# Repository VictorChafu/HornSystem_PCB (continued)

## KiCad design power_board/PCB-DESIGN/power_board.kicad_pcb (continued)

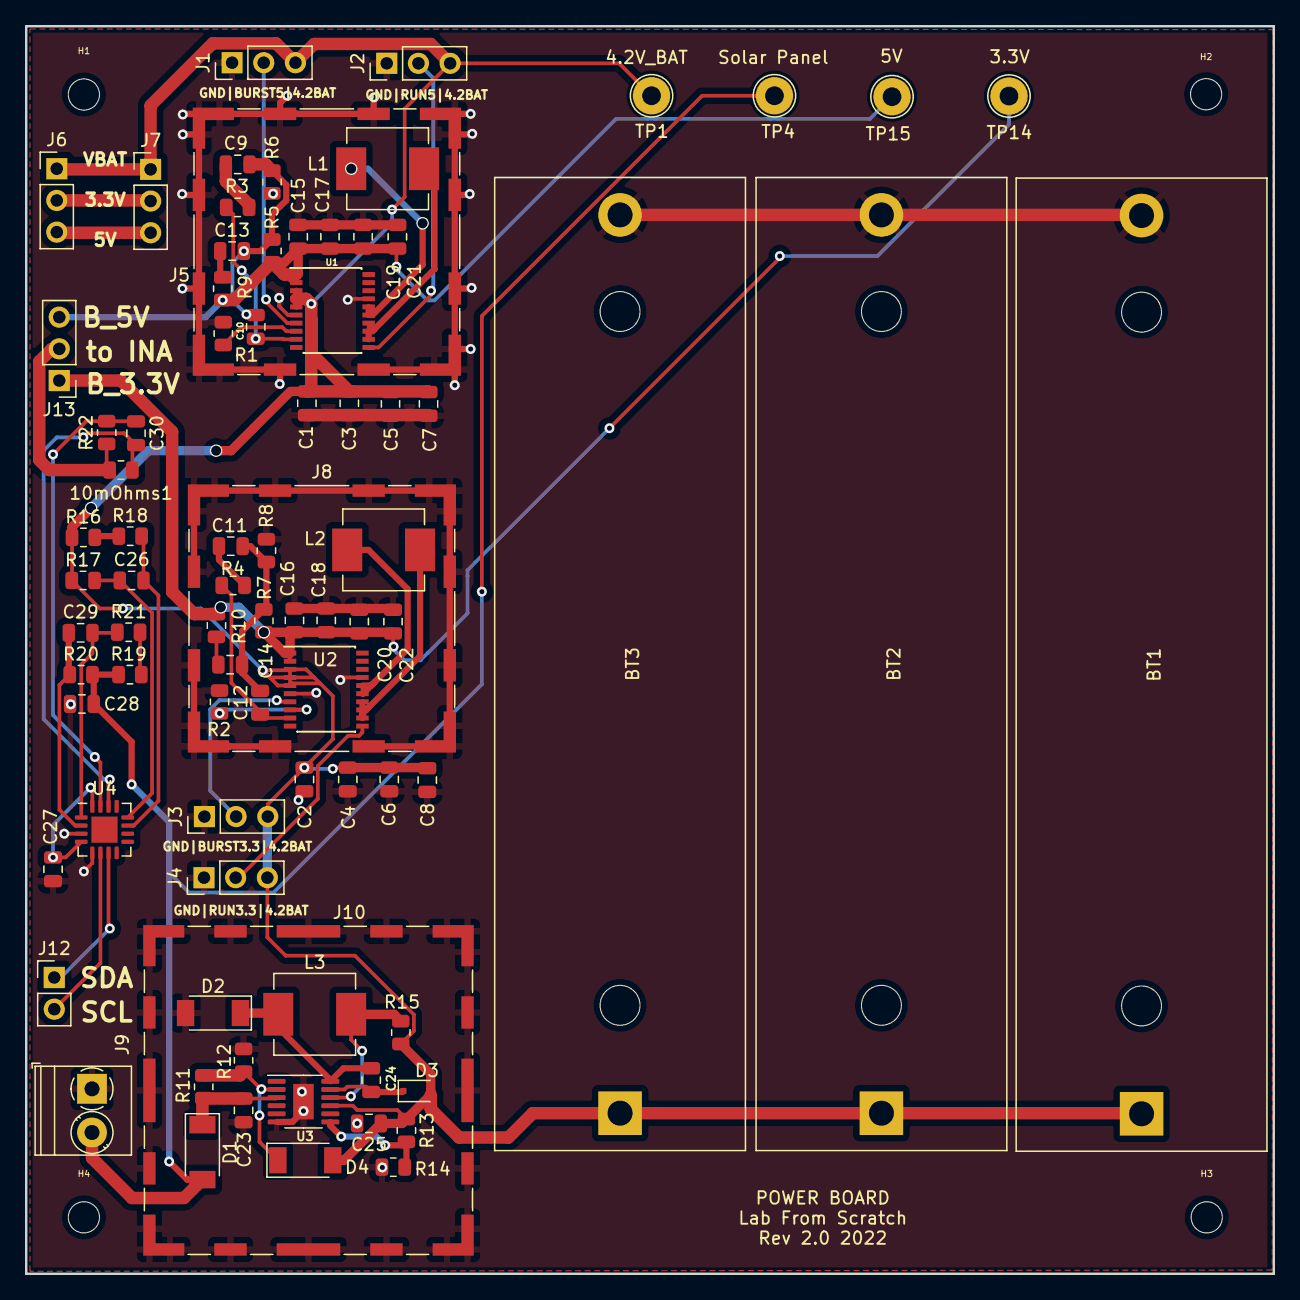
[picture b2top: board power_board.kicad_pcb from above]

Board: 4 copper layers, 100.0 x 100.0 mm, 87 parts (0 on the bottom side), 43 nets.
